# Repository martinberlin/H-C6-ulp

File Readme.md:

### ESP32-C6 ULP mini PCB

This PCB design is based on [C6 design guidelines](https://docs.espressif.com/projects/esp-hardware-design-guidelines/en/latest/esp32c6/schematic-checklist.html) and uses the Buck converter schematic of Seeed XIAO C6 [SGM6029](https://www.sg-micro.com/product/SGM6029)

> The SGM6029 family is a low voltage, efficient and miniature synchronous Buck converter with ultra-low quiescent current. Operating at high switching frequency (4.0MHz, TYP), miniature inductors and capacitors can be used to achieve minimal solution size.

#### Using low GPIOs to be able to access them from ULP

```
IO Description
0 EPD_MOSI
1 EPD_CLK
2 EPD_CS
3 EPD_DC
4 EPD_BSY
5 EPD_RST
6 SCL --> I2C ↘
7 SDA --> I2C connected to RV2032 RTC
```

### Push buttons GPIOs (optional side switches)

```
IO Description
19 Left  SW1 
20 Right SW2
18 Right SW3
```

### 3D-Preview

Last version 1.1:

Failed release v1.0: We forgot to add SPI flash. Oh yeah, you won't flash it!

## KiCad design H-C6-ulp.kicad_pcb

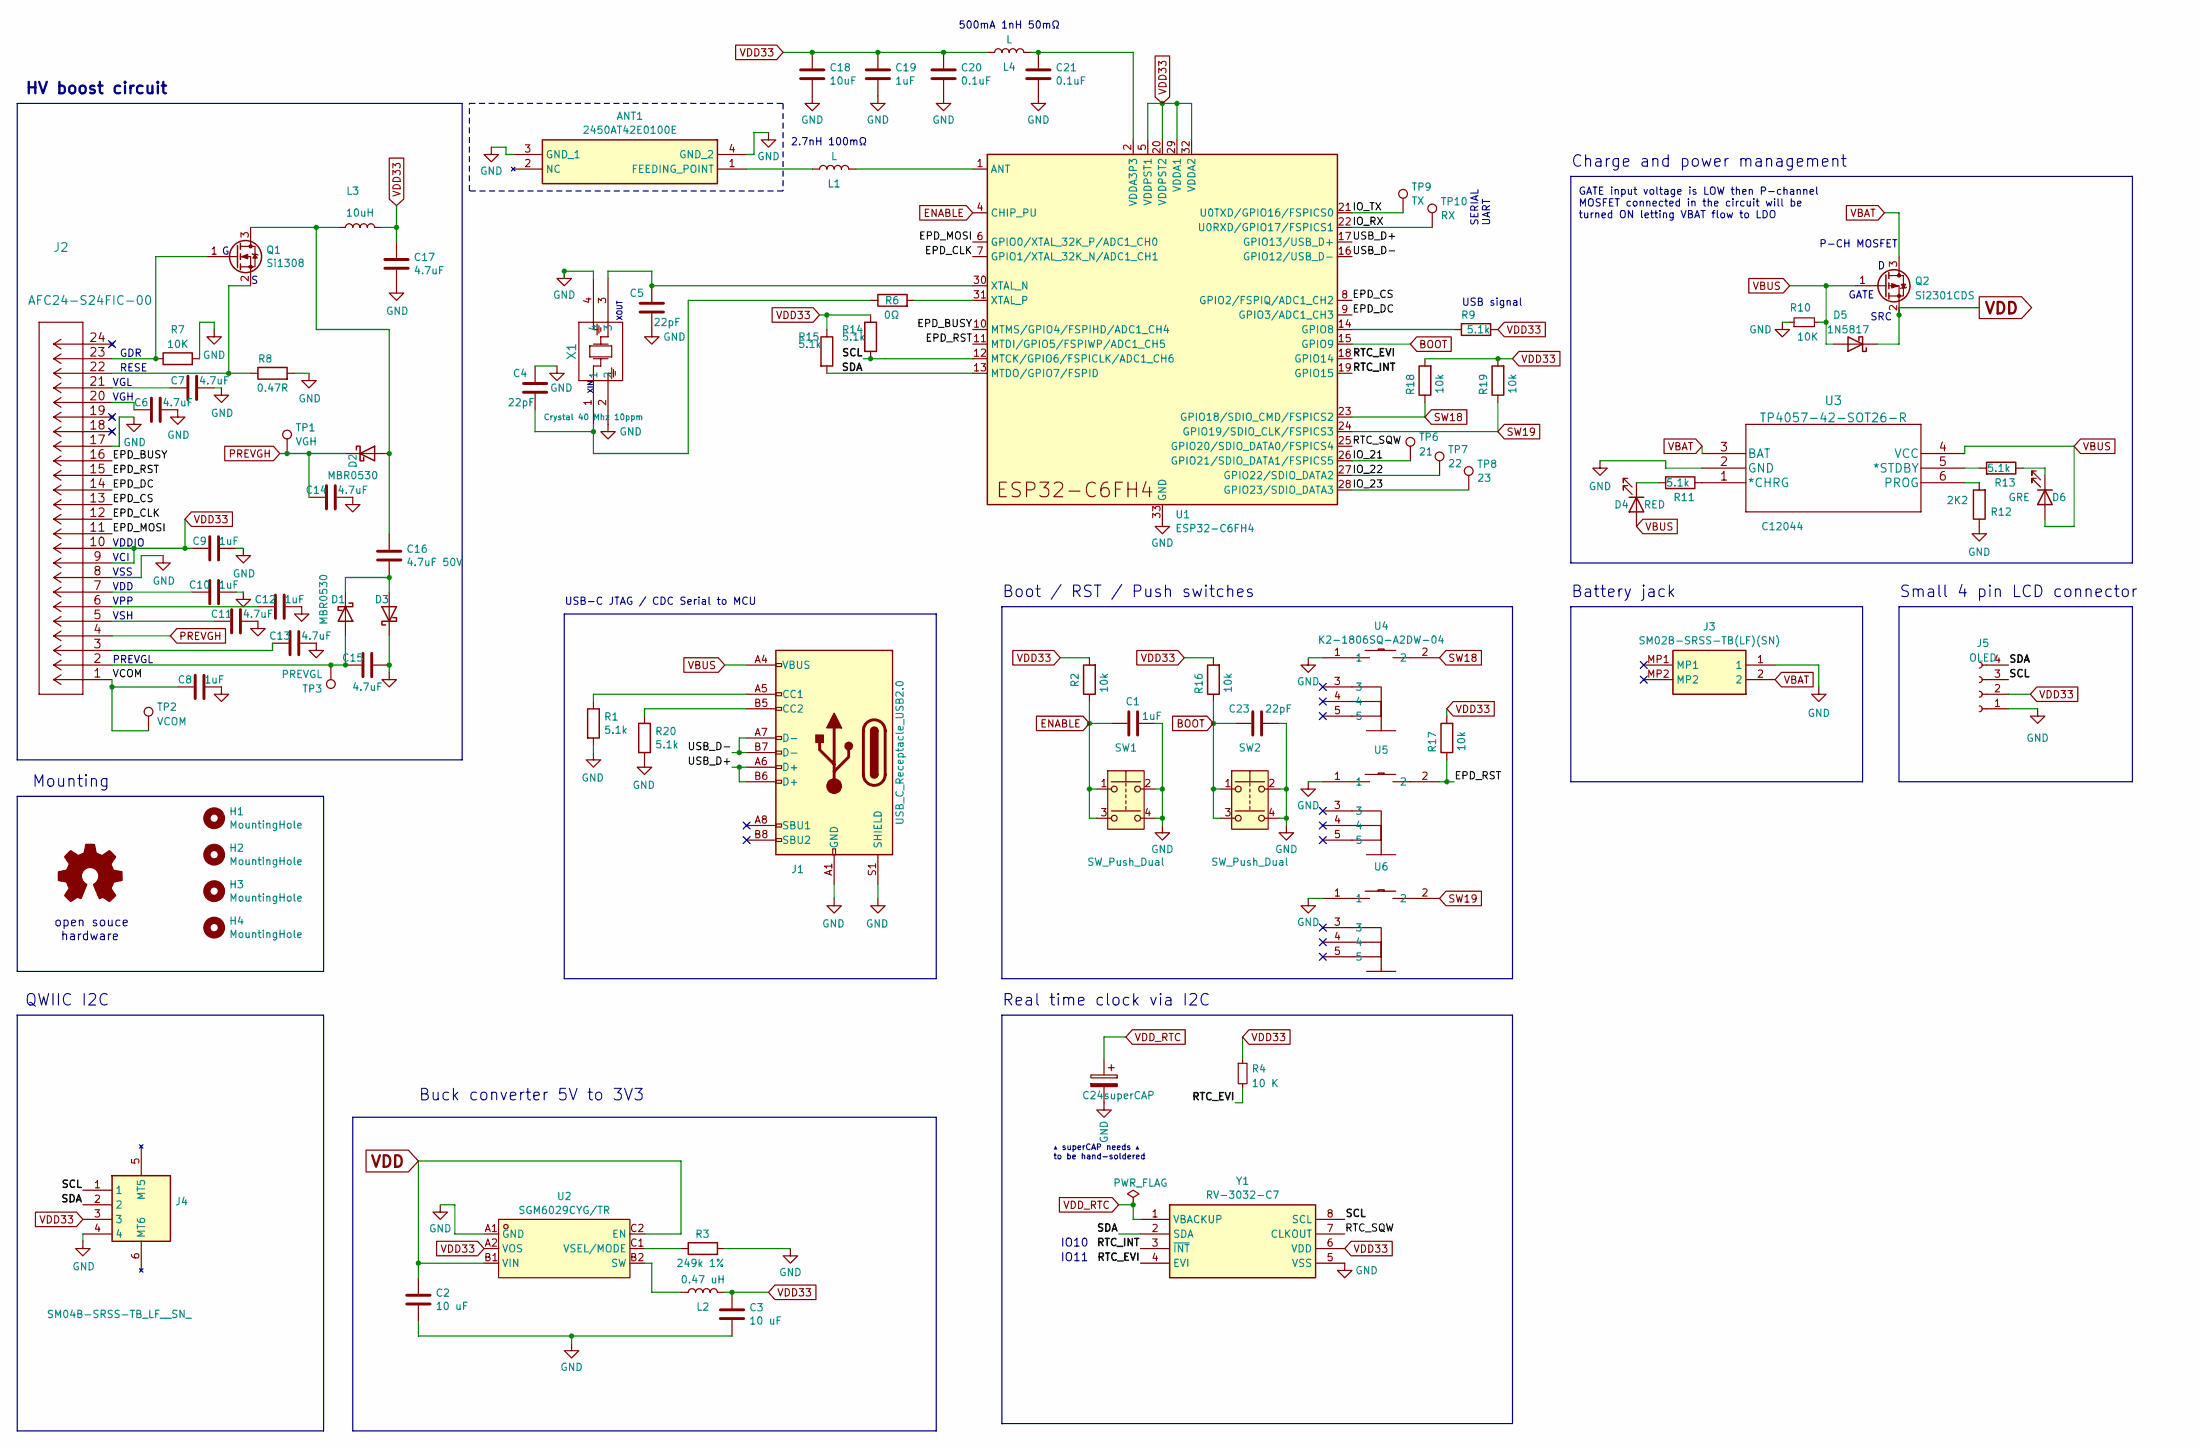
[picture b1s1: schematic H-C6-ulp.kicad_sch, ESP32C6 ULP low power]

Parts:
ANT1: 2450AT42E0100E; 2450AT42E0100E-ANT; LCSC C3285081
C1, C19: 1uF; C_0402_1005Metric; LCSC C162161
C2, C3: 10 uF; C_0603_1608Metric; LCSC C6119874
C4, C5, C23: 22pF; C_0402_1005Metric; LCSC C5119318
C6, C7, C11, C13, C14, C15: 4.7uF; C_0805_2012Metric_Pad1.18x1.45mm_HandSolder; LCSC C1779
C8, C9, C10, C12: 1uF; C_0805_2012Metric_Pad1.18x1.45mm_HandSolder; LCSC C28323
C16: 4.7uF 50V; C_0805_2012Metric_Pad1.18x1.45mm_HandSolder; LCSC C1779
C17: 4.7uF; C_0603_1608Metric; LCSC C19666
C18: 10uF; C_0805_2012Metric; LCSC C15850
C20, C21: 0.1uF; C_0603_1608Metric; LCSC C327087
C24: superCAP; superCAP-XH414HG; LCSC C129289
D1, D2, D3: MBR0530; D_SOD-123; LCSC C77336
D4: RED; LED_0805_2012Metric; LCSC C84256
D5: 1N5817; D_SOD-123; LCSC C8598
D6: GRE; LED_0805_2012Metric; LCSC C2297
H1, H2, H3, H4: MountingHole; MountingHole_2.2mm_M2
J1: USB_C_Receptacle_USB2.0; USB_C_Receptacle_HRO_TYPE-C-31-M-12; LCSC C165948
J2: AFC24-S24FIC-00; LCSC C262292
J3: SM02B-SRSS-TB(LF)(SN); SM02BSRSSTBLFSN; Manufacturer_Part_Number SM02B-SRSS-TB(LF)(SN); LCSC C160402
J4: SM04B-SRSS-TB_LF__SN_; QWIIC_SM04B-SRSS-TB_LFSN_; Manufacturer_Part_Number SM04B-SRSS-TB(LF)(SN); LCSC C160404
J5: OLED; PinSocket_1x04_P2.54mm_Vertical
L1: L; L_0603_1608Metric; LCSC C5252358
L2: 0.47 uH; IND-SMD_L2.5-W2.0_SPH252012; LCSC C329586
L3: 10uH; SWPA4030S1R0NT; LCSC C38117
L4: L; L_0603_1608Metric; LCSC C1027
Q1: Si1308; SOT-323_SC-70; LCSC C469327
Q2: Si2301CDS; SOT-23; LCSC C10487
R1, R9, R11, R13, R14, R15, R20: 5.1k; R_0603_1608Metric; LCSC C23186
R2, R16, R17, R18, R19: 10k; R_0402_1005Metric; LCSC C4322213
R3: 249k 1%; R_0603_1608Metric; LCSC C6945215
R4: 10 K; R_0402_1005Metric; LCSC C4322213
R6: 0Ω; R_0603_1608Metric; LCSC C21189
R7: 10K; R_0402_1005Metric; LCSC C4322213
R8: 0.47R; R_0603_1608Metric; LCSC C103895
R10: 10K; R_0402_1005Metric; LCSC C25804
R12: 2K2; R_0805_2012Metric; LCSC C17520
SW1, SW2: SW_Push_Dual; switch_SKSVCCE010; LCSC C325005
TP1: VGH; TestPoint_Pad_D1.5mm
TP2: VCOM; TestPoint_Pad_D1.5mm
TP3: PREVGL; TestPoint_Pad_D1.5mm
TP6: 21; TestPoint_Pad_D1.0mm
TP7: 22; TestPoint_Pad_D1.0mm
TP8: 23; TestPoint_Pad_D1.0mm
TP9: TX; TestPoint_Pad_D1.0mm
TP10: RX; TestPoint_Pad_D1.0mm
U1: ESP32-C6FH4; QFN-32-1EP_5x5mm_P0.5mm_EP3.6x3.6mm; LCSC C6908287
U2: SGM6029CYG/TR; SGM6029_WLCSP-6; LCSC Part C5153500
U3: TP4057-42-SOT26-R; LCSC C12044
U4, U5, U6: K2-1806SQ-A2DW-04; KEY-SMD_K2-1806SQ-A3DW-04; LCSC Part C19100323
X1: Crystal 40 Mhz 10ppm; Crystal_ECS-40Mhz_ECS; LCSC C555614
Y1: RV-3032-C7; RV3032C7; LCSC C5127802

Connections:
/EPD_BUSY: J2.16, U1.10 (MTMS/GPIO4/FSPIHD/ADC1_CH4)
/EPD_CLK: J2.12, U1.7 (GPIO1/XTAL_32K_N/ADC1_CH1)
/EPD_CS: J2.13, U1.8 (GPIO2/FSPIQ/ADC1_CH2)
/EPD_DC: J2.14, U1.9 (GPIO3/ADC1_CH3)
/EPD_MOSI: J2.11, U1.6 (GPIO0/XTAL_32K_P/ADC1_CH0)
/EPD_RST: J2.15, R17.1, U1.11 (MTDI/GPIO5/FSPIWP/ADC1_CH5), U5.2
/IO_21: TP6.1, U1.26 (GPIO21/SDIO_DATA1/FSPICS5)
/IO_22: TP7.1, U1.27 (GPIO22/SDIO_DATA2)
/IO_23: TP8.1, U1.28 (GPIO23/SDIO_DATA3)
/IO_RX: TP10.1, U1.22 (U0RXD/GPIO17/FSPICS1)
/IO_TX: TP9.1, U1.21 (U0TXD/GPIO16/FSPICS0)
/RTC_EVI: R4.2, U1.18 (GPIO14), Y1.4 (EVI)
/RTC_INT: U1.19 (GPIO15), Y1.3 (~INT)
/RTC_SQW: U1.25 (GPIO20/SDIO_DATA0/FSPICS4), Y1.7 (CLKOUT)
/SCL: J4.1, J5.3, R14.2, U1.12 (MTCK/GPIO6/FSPICLK/ADC1_CH6), Y1.8 (SCL)
/SDA: J4.2, J5.4, R15.2, U1.13 (MTDO/GPIO7/FSPID), Y1.2 (SDA)
/USB_D+: J1.A6 (D+), J1.B6 (D+), U1.17 (GPIO13/USB_D+)
/USB_D-: J1.A7 (D-), J1.B7 (D-), U1.16 (GPIO12/USB_D-)
/VCOM: C8.2, J2.1, TP2.1
BOOT: C23.1, R16.1, SW2.1, SW2.3, U1.15 (GPIO9)
ENABLE: C1.2, R2.1, SW1.1, SW1.3, U1.4 (CHIP_PU)
GND: ANT1.3 (GND_1), ANT1.4 (GND_2), C1.1, C2.1, C3.1, C4.1, C5.2, C6.1, C7.1, C8.1, C9.1, C10.1, C11.1, C12.1, C13.1, C14.1, C15.1, C17.1, C18.1, C19.1, C20.1, C21.1, C23.2, C24.2, D3.1 (K), J1.A1 (GND), J1.A12 (GND), J1.B1 (GND), J1.B12 (GND), J1.S1 (SHIELD), J2.8, J2.17, J3.1, J4.4, J5.1, R1.2, R3.2, R7.2, R8.2, R10.1, R12.1, R20.2, SW1.2, SW1.4, SW2.2, SW2.4, U1.33 (GND), U2.A1 (GND), U3.2 (GND), U4.1, U5.1, U6.1, X1.2, X1.4, Y1.5 (VSS)
unnamed: ANT1.1 (FEEDING_POINT), L1.1
unnamed: C4.2, R6.1, X1.1
unnamed: C6.2, J2.20
unnamed: C7.2, J2.21
unnamed: C10.2, J2.7
unnamed: C11.2, J2.5
unnamed: C12.2, J2.6
unnamed: C13.2, J2.3
unnamed: C21.2, L4.2, U1.2 (VDDA3P3), U1.3 (VDDA3P3)
unnamed: C15.2, D1.2 (A), J2.2, TP3.1
unnamed: C16.1, D1.1 (K), D3.2 (A)
unnamed: C16.2, D2.2 (A), L3.1, Q1.3 (D)
unnamed: D4.1 (K), R11.2
unnamed: D6.1 (K), R13.1
unnamed: J1.A5 (CC1), R1.1
unnamed: J1.B5 (CC2), R20.1
unnamed: J2.23, Q1.1 (G), R7.1
unnamed: J2.22, Q1.2 (S), R8.1
unnamed: L1.2, U1.1 (ANT)
unnamed: R9.1, U1.14 (GPIO8)
unnamed: C5.1, U1.30 (XTAL_N), X1.3
unnamed: R6.2, U1.31 (XTAL_P)
unnamed: L2.1, U2.B2 (SW)
unnamed: R3.1, U2.C1 (VSEL/MODE)
unnamed: R11.1, U3.1 (*CHRG)
unnamed: R13.2, U3.5 (*STDBY)
unnamed: R12.2, U3.6 (PROG)
PREVGH: C14.2, D2.1 (K), J2.4, TP1.1
SW18: R18.1, U1.23 (GPIO18/SDIO_CMD/FSPICS2), U4.2
SW19: R19.1, U1.24 (GPIO19/SDIO_CLK/FSPICS3), U6.2
VBAT: J3.2, Q2.3 (D), U3.3 (BAT)
VBUS: D4.2 (A), D5.2 (A), D6.2 (A), J1.A4 (VBUS), J1.A9 (VBUS), J1.B4 (VBUS), J1.B9 (VBUS), Q2.1 (G), R10.2, U3.4 (VCC)
VDD: C2.2, D5.1 (K), Q2.2 (S), U2.B1 (VIN), U2.C2 (EN)
VDD33: C3.2, C9.2, C17.2, C18.2, C19.2, C20.2, J2.9, J2.10, J4.3, J5.2, L2.2, L3.2, L4.1, R2.2, R4.1, R9.2, R14.1, R15.1, R16.2, R17.2, R18.2, R19.2, U1.5 (VDDPST1), U1.20 (VDDPST2), U1.29 (VDDA1), U1.32 (VDDA2), U2.A2 (VOS), Y1.6 (VDD)
VDD_RTC: C24.1, Y1.1 (VBACKUP)

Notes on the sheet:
USB-C JTAG / CDC Serial to MCU
Mounting
IO10
VGH
RESE
VGL
HV boost circuit
Buck converter 5V to 3V3
XOUT
Real time clock via I2C
500mA 1nH 50mΩ
Small 4 pin LCD connector
VSH
VPP
QWIIC I2C
SRC
GATE
open souce hardware
GDR
P-CH MOSFET
Battery jack
▴ superCAP needs ▴ to be hand-soldered
IO11
Boot / RST / Push switches
VDDIO
GATE input voltage is LOW then P-channel MOSFET connected in the circuit will be turned ON letting VBAT flow to LDO
USB signal
PREVGL
XIN
2.7nH 100mΩ
VSS
VCI
Charge and power management
SERIAL UART
VDD

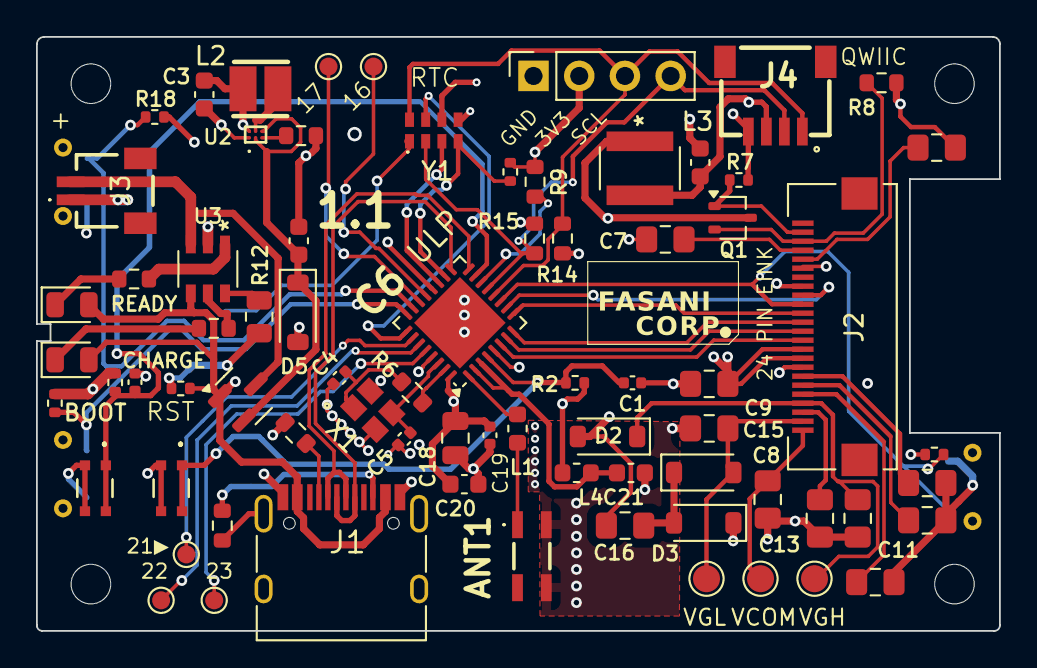
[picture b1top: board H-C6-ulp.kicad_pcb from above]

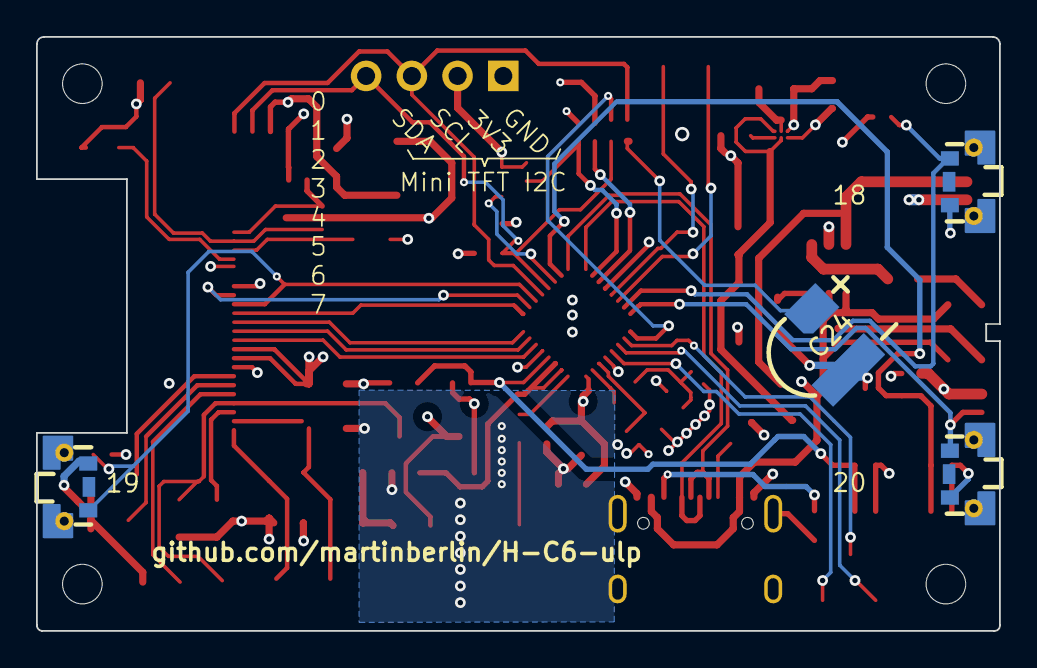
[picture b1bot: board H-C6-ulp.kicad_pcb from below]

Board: 4 copper layers, 53.5 x 33.0 mm, 82 parts (4 on the bottom side), 57 nets.

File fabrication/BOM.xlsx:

Designator | Footprint | Comment | JLCPCB Part #
C14,C11,C6,C7,C15,C13 | C_0805_2012Metric_Pad1.18x1.45mm_HandSolder | 4.7uF | C1779
D5 | D_SOD-123 | 1N5817 | C8598
R17,R2,R18,R19,R16,R7,R4,R10 | R_0402_1005Metric | 10k | C25804
C1,C19 | C_0402_1005Metric | 1uF | C162161
C2,C3 | C_0603_1608Metric | 10 uF | C6119874
C5,C23,C4 | C_0402_1005Metric | 22pF | C5119318
R6 | R_0603_1608Metric | 0Ω | C21189
D2,D1,D3 | D_SOD-123 | MBR0530 | C77336
U3 | TP4057-42-SOT26-R | TP4057-42-SOT26-R | C12044
L2 | IND-SMD_L2.5-W2.0_SPH252012 | 0.47 uH | C329586
L3 | SWPA4030S1R0NT | 10uH | C38117
C8,C9,C10,C12 | C_0805_2012Metric_Pad1.18x1.45mm_HandSolder | 1uF | C28323
J3 | SM02BSRSSTBLFSN | SM02B-SRSS-TB(LF)(SN) | C160402
L1,L4 | L_0603_1608Metric | L | C5252358
R15,R20,R14,R13,R1,R9,R11 | R_0603_1608Metric | 5.1k | C23186
C20,C21 | C_0603_1608Metric | 0.1uF | C327087
SW2,SW1 | switch_SKSVCCE010 | SW_Push_Dual | C325005
C16 | C_0805_2012Metric_Pad1.18x1.45mm_HandSolder | 4.7uF 50V | C1779
C18 | C_0805_2012Metric | 10uF | C15850
C17 | C_0603_1608Metric | 4.7uF | C19666
R3 | R_0603_1608Metric | 249k 1% | C6945215
X1 | Crystal_ECS-40Mhz_ECS | Crystal 40 Mhz 10ppm | C555614
R12 | R_0805_2012Metric | 2K2 | C17520
J1 | USB_C_Receptacle_HRO_TYPE-C-31-M-12 | USB_C_Receptacle_USB2.0 | C165948
ANT1 | 2450AT42E0100E-ANT | 2450AT42E0100E | C3285081
Y1 | RV3032C7 | RV-3032-C7 | C5127802
D6 | LED_0805_2012Metric | GRE | C2297
J2 | AFC24-S24FIC-00 | AFC24-S24FIC-00 | C262292
R8 | R_0603_1608Metric | 0.47R | C103895
U2 | SGM6029_WLCSP-6 | SGM6029CYG/TR | C5153500
Q2 | SOT-23 | Si2301CDS | C10487
U1 | QFN-32-1EP_5x5mm_P0.5mm_EP3.6x3.6mm | ESP32-C6FH4 | C6908287
Q1 | SOT-323_SC-70 | Si1308 | C4322213
D4 | LED_0805_2012Metric | RED | C84256
J4 | QWIIC_SM04B-SRSS-TB_LFSN_ | SM04B-SRSS-TB_LF__SN_ | C160404

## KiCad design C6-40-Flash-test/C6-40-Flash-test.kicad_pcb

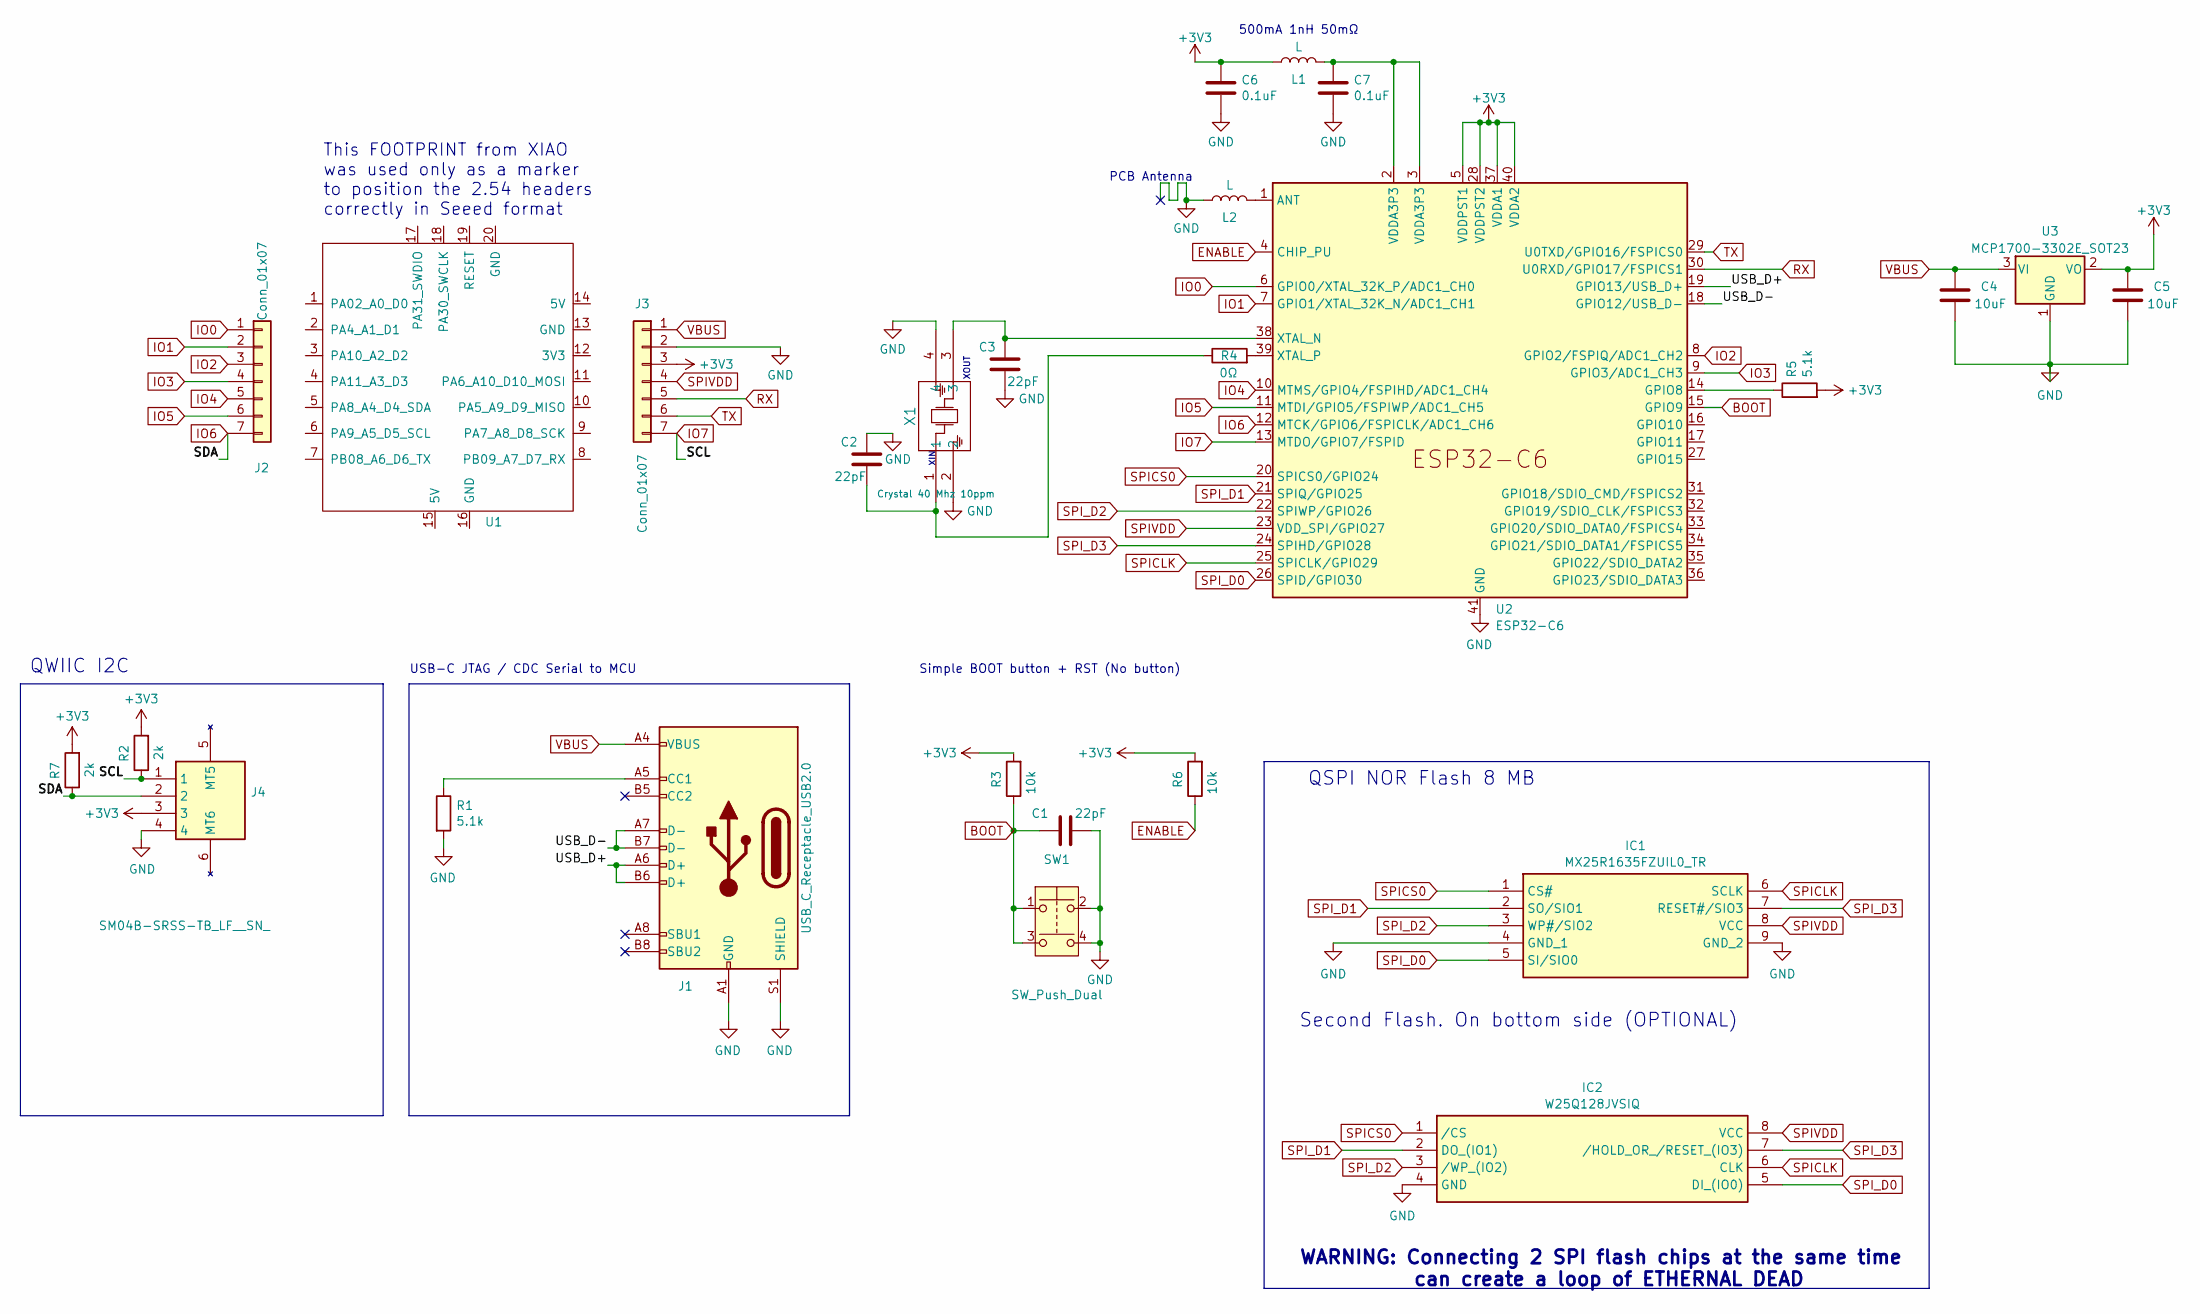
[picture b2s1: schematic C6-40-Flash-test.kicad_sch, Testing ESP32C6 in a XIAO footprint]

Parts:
C1, C2, C3: 22pF; C_0402_1005Metric; LCSC C5119318
C4, C5: 10uF; C_0805_2012Metric; LCSC C15850
C6, C7: 0.1uF; C_0603_1608Metric; LCSC C327087
IC1: MX25R1635FZUIL0_TR; MX25R1635FZUIL0TR; LCSC C152595
IC2: W25Q128JVSIQ; SOIC127P790X216-8N; Manufacturer_Part_Number W25Q128JVSIQ; Mouser Part Number 454-W25Q128JVSIQ
J1: USB_C_Receptacle_USB2.0; USB_C_Receptacle_HRO_TYPE-C-31-M-12; LCSC C165948
J2, J3: Conn_01x07; PinSocket_1x07_P2.54mm_Vertical
J4: SM04B-SRSS-TB_LF__SN_; QWIIC_SM04B-SRSS-TB_LFSN_; Manufacturer_Part_Number SM04B-SRSS-TB(LF)(SN); LCSC C160404
L1: L; L_0603_1608Metric; LCSC C1027
L2: L; L_0603_1608Metric; LCSC C5252358
R1, R5: 5.1k; R_0603_1608Metric; LCSC C23186
R2, R7: 2k; R_0402_1005Metric; LCSC C4109
R3, R6: 10k; R_0402_1005Metric; LCSC C4322213
R4: 0Ω; R_0603_1608Metric; LCSC C21189
SW1: SW_Push_Dual; switch_SKSVCCE010; LCSC C325005
U1: SeeeduinoXIAO; Seeeduino XIAO-MOUDLE14P-2.54-21X17.8MM
U2: ESP32-C6; QFN-40-1EP_5x5mm_P0.4mm_EP3.6x3.6mm; LCSC C5364646
U3: MCP1700-3302E_SOT23; SOT-23; LCSC C39051
X1: Crystal 40 Mhz 10ppm; Crystal_ECS-40Mhz_ECS; LCSC C555614

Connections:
+3V3: C5.1, C6.2, J3.3, J4.3, L1.1, R2.2, R3.2, R5.2, R6.2, R7.2, U2.5 (VDDPST1), U2.28 (VDDPST2), U2.37 (VDDA1), U2.40 (VDDA2), U3.2 (VO)
/USB_D+: J1.A6 (D+), J1.B6 (D+), U2.19 (GPIO13/USB_D+)
/USB_D-: J1.A7 (D-), J1.B7 (D-), U2.18 (GPIO12/USB_D-)
BOOT: C1.1, R3.1, SW1.1, SW1.3, U2.15 (GPIO9)
ENABLE: R6.1, U2.4 (CHIP_PU)
GND: C1.2, C2.1, C3.2, C4.2, C5.2, C6.1, C7.1, IC1.4 (GND_1), IC1.9 (GND_2), IC2.4 (GND), J1.A1 (GND), J1.A12 (GND), J1.B1 (GND), J1.B12 (GND), J1.S1 (SHIELD), J3.2, J4.4, L2.1, R1.2, SW1.2, SW1.4, U2.41 (GND), U3.1 (GND), X1.2, X1.4
IO0: J2.1, U2.6 (GPIO0/XTAL_32K_P/ADC1_CH0)
IO1: J2.2, U2.7 (GPIO1/XTAL_32K_N/ADC1_CH1)
IO2: J2.3, U2.8 (GPIO2/FSPIQ/ADC1_CH2)
IO3: J2.4, U2.9 (GPIO3/ADC1_CH3)
IO4: J2.5, U2.10 (MTMS/GPIO4/FSPIHD/ADC1_CH4)
IO5: J2.6, U2.11 (MTDI/GPIO5/FSPIWP/ADC1_CH5)
IO6: J2.7, J4.2, R7.1, U2.12 (MTCK/GPIO6/FSPICLK/ADC1_CH6)
IO7: J3.7, J4.1, R2.1, U2.13 (MTDO/GPIO7/FSPID)
unnamed: C2.2, R4.1, X1.1
unnamed: C7.2, L1.2, U2.2 (VDDA3P3), U2.3 (VDDA3P3)
unnamed: J1.A5 (CC1), R1.1
unnamed: L2.2, U2.1 (ANT)
unnamed: R5.1, U2.14 (GPIO8)
unnamed: C3.1, U2.38 (XTAL_N), X1.3
unnamed: R4.2, U2.39 (XTAL_P)
RX: J3.5, U2.30 (U0RXD/GPIO17/FSPICS1)
SPICLK: IC1.6 (SCLK), IC2.6 (CLK), U2.25 (SPICLK/GPIO29)
SPICS0: IC1.1 (CS#), IC2.1 (/CS), U2.20 (SPICS0/GPIO24)
SPIVDD: IC1.8 (VCC), IC2.8 (VCC), J3.4, U2.23 (VDD_SPI/GPIO27)
SPI_D0: IC1.5 (SI/SIO0), IC2.5 (DI_(IO0)), U2.26 (SPID/GPIO30)
SPI_D1: IC1.2 (SO/SIO1), IC2.2 (DO_(IO1)), U2.21 (SPIQ/GPIO25)
SPI_D2: IC1.3 (WP#/SIO2), IC2.3 (/WP_(IO2)), U2.22 (SPIWP/GPIO26)
SPI_D3: IC1.7 (RESET#/SIO3), IC2.7 (/HOLD_OR_/RESET_(IO3)), U2.24 (SPIHD/GPIO28)
TX: J3.6, U2.29 (U0TXD/GPIO16/FSPICS0)
VBUS: C4.1, J1.A4 (VBUS), J1.A9 (VBUS), J1.B4 (VBUS), J1.B9 (VBUS), J3.1, U3.3 (VI)

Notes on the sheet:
QSPI NOR Flash 8 MB
Second Flash. On bottom side (OPTIONAL)
XOUT
USB-C JTAG / CDC Serial to MCU
Simple BOOT button + RST (No button)
WARNING: Connecting 2 SPI flash chips at the same time can create a loop of ETHERNAL DEAD
This FOOTPRINT from XIAO was used only as a marker to position the 2.54 headers correctly in Seeed format
PCB Antenna
XIN
QWIIC I2C
500mA 1nH 50mΩ

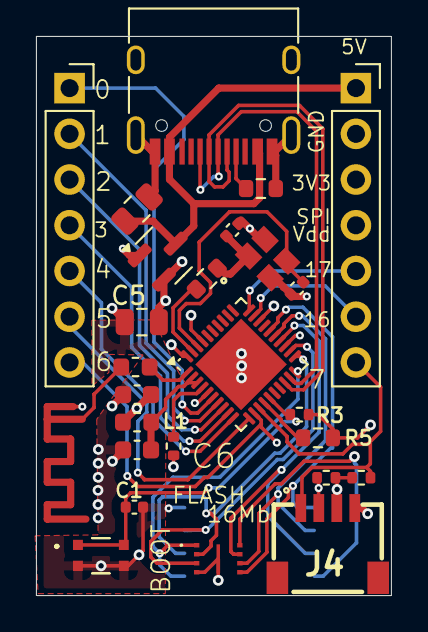
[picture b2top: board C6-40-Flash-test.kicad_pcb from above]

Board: 4 copper layers, 19.7 x 31.1 mm, 26 parts (1 on the bottom side), 31 nets.

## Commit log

2024-09-10 Initial
2024-09-10 Remove backups
2024-09-10 Remove lck
2024-09-13 First version passing DRC
2024-09-13 Add QWIIC I2c connector
2024-09-15 Rev 1.0 is quite ready for last review @bitbank2
2024-09-15 Move mounting H out of display area
2024-09-15 Add BOOT & RST switches
2024-09-15 3 buttons, a bit risky routing
2024-09-16 Add Readme
2024-09-16 Add pull-ups
2024-09-16 Update L2 with same inductor 470nH than XIAO C6
2024-09-17 Add superCAP as RTC backup
2024-09-17 Update front img
2024-09-17 Fix #2 Thanks @Uspizig
2024-09-24 Add 1mm TP for coin battery (Passes through regulator also)
2024-10-23 Add QSPI Flash
2024-10-23 Flash oh oh! Master of the universe
2024-10-24 Add small XIAO format C6 tester w/FLASH
2024-10-24 Make antenna better (Is a shoelace)
2024-10-24 C6 test new Flash
2024-11-12 Test with external flash
2024-11-22 C6-ulp-schematic_Rev1.
2024-11-22 Update 1.1 SCH with 4 MB Flash MCU
2024-11-23 1.1 ready for review
2024-11-23 Cleanup
2024-11-25 Saving 1.1 state before making it 51 mm
2024-11-26 Rel 1.1 ready
2024-12-13 Fix epaper power
2024-12-16 Update Schematic

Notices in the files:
parts and their libraries:
Copyright 2021 Accelerated Designs. All rights reserved.
